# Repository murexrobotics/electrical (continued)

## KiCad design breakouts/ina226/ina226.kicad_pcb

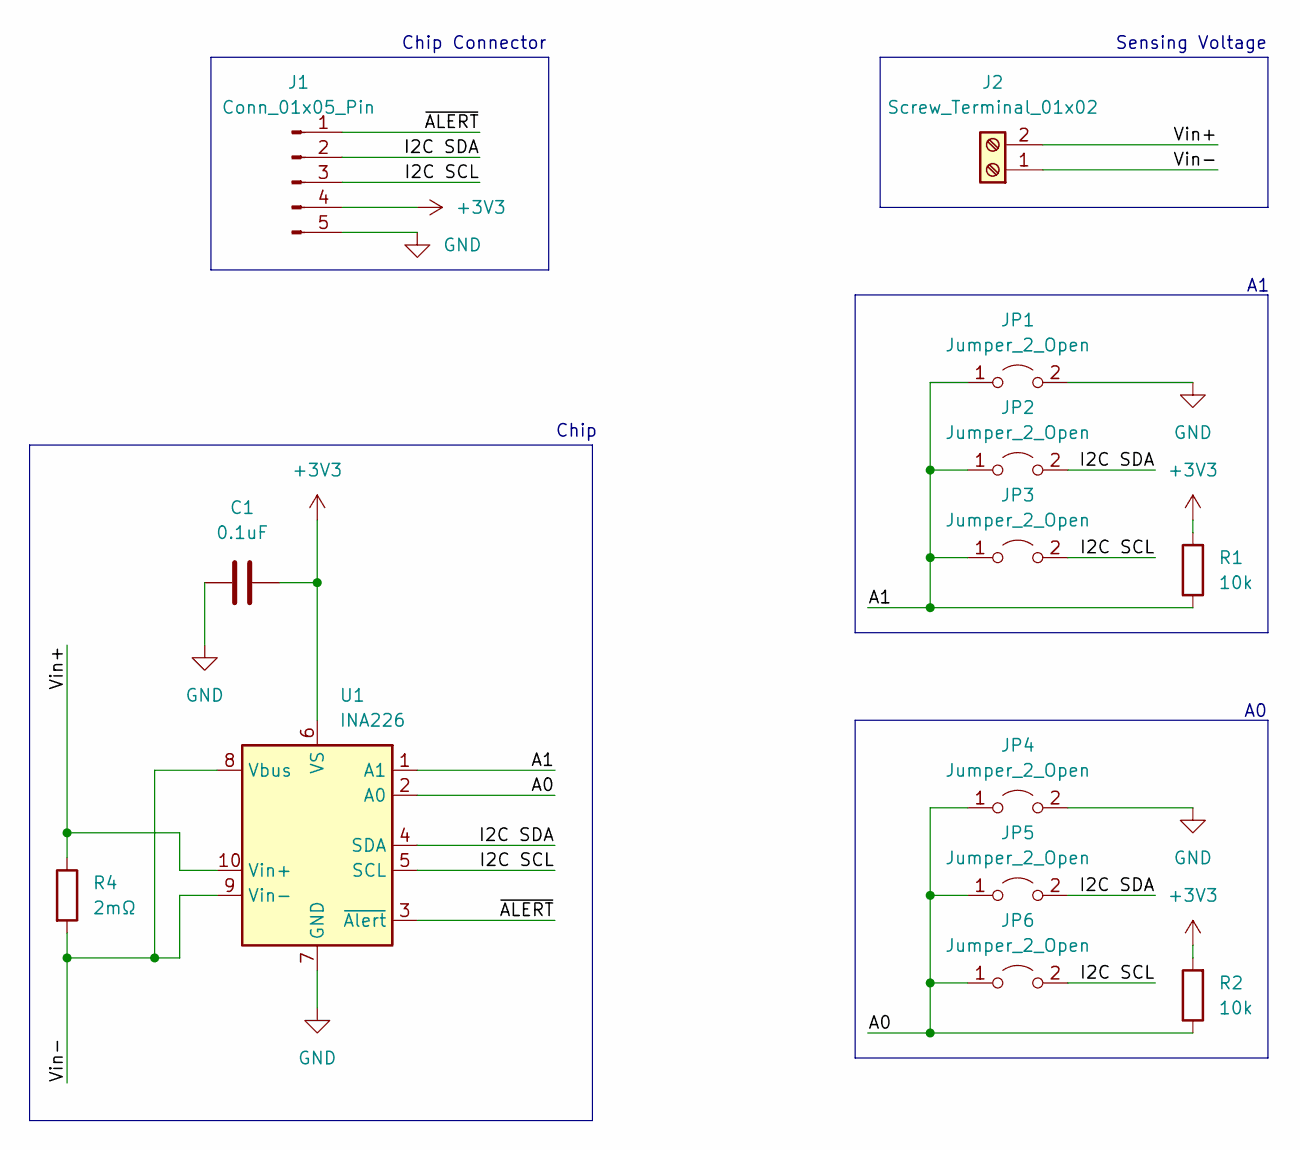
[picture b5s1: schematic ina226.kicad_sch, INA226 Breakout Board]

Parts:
C1: 0.1uF; C_0603_1608Metric
J1: Conn_01x05_Pin; PinHeader_1x05_P2.54mm_Vertical
J2: Screw_Terminal_01x02; CONN_1935776_PXC
JP1, JP2, JP3, JP4, JP5, JP6: Jumper_2_Open; SolderJumper-2_P1.3mm_Open_Pad1.0x1.5mm
R1, R2: 10k; R_0603_1608Metric
R4: 2mΩ; R_2512_6332Metric
U1: INA226; VSSOP-10_3x3mm_P0.5mm

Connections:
+3V3: C1.2, J1.4, R1.2, R2.2, U1.6 (VS)
/A0: JP4.1 (A), JP5.1 (A), JP6.1 (A), R2.1, U1.2 (A0)
/A1: JP1.1 (A), JP2.1 (A), JP3.1 (A), R1.1, U1.1 (A1)
/I2C SCL: J1.3, JP3.2 (B), JP6.2 (B), U1.5 (SCL)
/I2C SDA: J1.2, JP2.2 (B), JP5.2 (B), U1.4 (SDA)
/Vin+: J2.2, R4.1, U1.10 (Vin+)
/Vin-: J2.1, R4.2, U1.8 (Vbus), U1.9 (Vin-)
/~ALERT: J1.1, U1.3 (~Alert)
GND: C1.1, J1.5, JP1.2 (B), JP4.2 (B), U1.7 (GND)

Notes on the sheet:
Chip
Sensing Voltage
Chip Connector

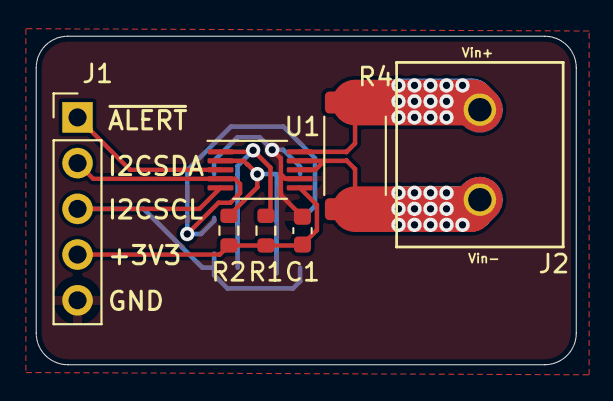
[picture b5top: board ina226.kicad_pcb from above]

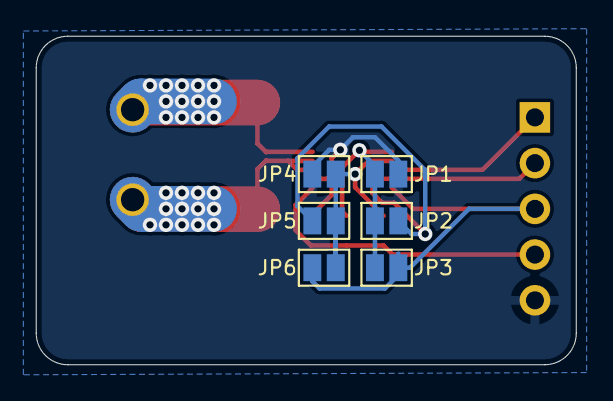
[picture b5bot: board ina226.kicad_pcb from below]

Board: 2 copper layers, 30.0 x 18.2 mm, 13 parts (6 on the bottom side), 9 nets.

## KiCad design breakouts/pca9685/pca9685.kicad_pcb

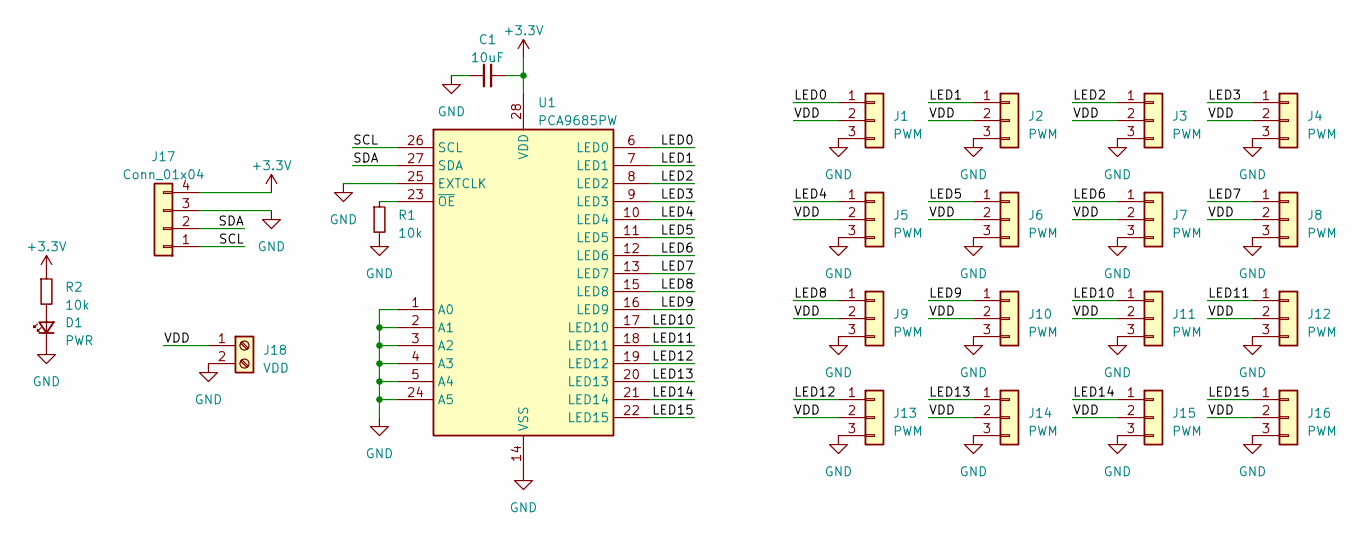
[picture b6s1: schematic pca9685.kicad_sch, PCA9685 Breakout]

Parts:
C1: 10uF; C_0603_1608Metric
D1: PWR; LED_0603_1608Metric
J1, J2, J3, J4, J5, J6, J7, J8, J9, J10, J11, J12, J13, J14, J15, J16: PWM; PinHeader_1x03_P2.54mm_Vertical
J17: Conn_01x04; PinHeader_1x04_P2.54mm_Vertical
J18: VDD; TerminalBlock_Altech_AK300-2_P5.00mm
R1, R2: 10k; R_0603_1608Metric
U1: PCA9685PW; TSSOP-28_4.4x9.7mm_P0.65mm

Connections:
+3.3V: C1.2, J17.4, R2.1, U1.28 (VDD)
/LED0: J1.1, U1.6 (LED0)
/LED1: J2.1, U1.7 (LED1)
/LED2: J3.1, U1.8 (LED2)
/LED3: J4.1, U1.9 (LED3)
/LED4: J5.1, U1.10 (LED4)
/LED5: J6.1, U1.11 (LED5)
/LED6: J7.1, U1.12 (LED6)
/LED7: J8.1, U1.13 (LED7)
/LED8: J9.1, U1.15 (LED8)
/LED9: J10.1, U1.16 (LED9)
/LED10: J11.1, U1.17 (LED10)
/LED11: J12.1, U1.18 (LED11)
/LED12: J13.1, U1.19 (LED12)
/LED13: J14.1, U1.20 (LED13)
/LED14: J15.1, U1.21 (LED14)
/LED15: J16.1, U1.22 (LED15)
/SCL: J17.1, U1.26 (SCL)
/SDA: J17.2, U1.27 (SDA)
/VDD: J1.2, J2.2, J3.2, J4.2, J5.2, J6.2, J7.2, J8.2, J9.2, J10.2, J11.2, J12.2, J13.2, J14.2, J15.2, J16.2, J18.1
GND: C1.1, D1.1 (K), J1.3, J2.3, J3.3, J4.3, J5.3, J6.3, J7.3, J8.3, J9.3, J10.3, J11.3, J12.3, J13.3, J14.3, J15.3, J16.3, J17.3, J18.2, R1.2, U1.1 (A0), U1.2 (A1), U1.3 (A2), U1.4 (A3), U1.5 (A4), U1.14 (VSS), U1.24 (A5), U1.25 (EXTCLK)
unnamed: D1.2 (A), R2.2
unnamed: R1.1, U1.23 (~OE)

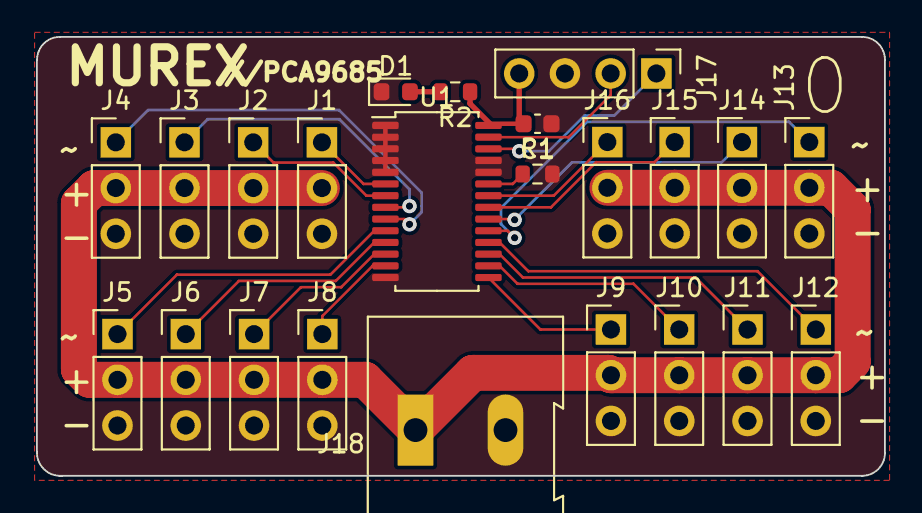
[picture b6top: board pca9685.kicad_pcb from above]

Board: 2 copper layers, 47.1 x 24.4 mm, 23 parts (0 on the bottom side), 23 nets.
